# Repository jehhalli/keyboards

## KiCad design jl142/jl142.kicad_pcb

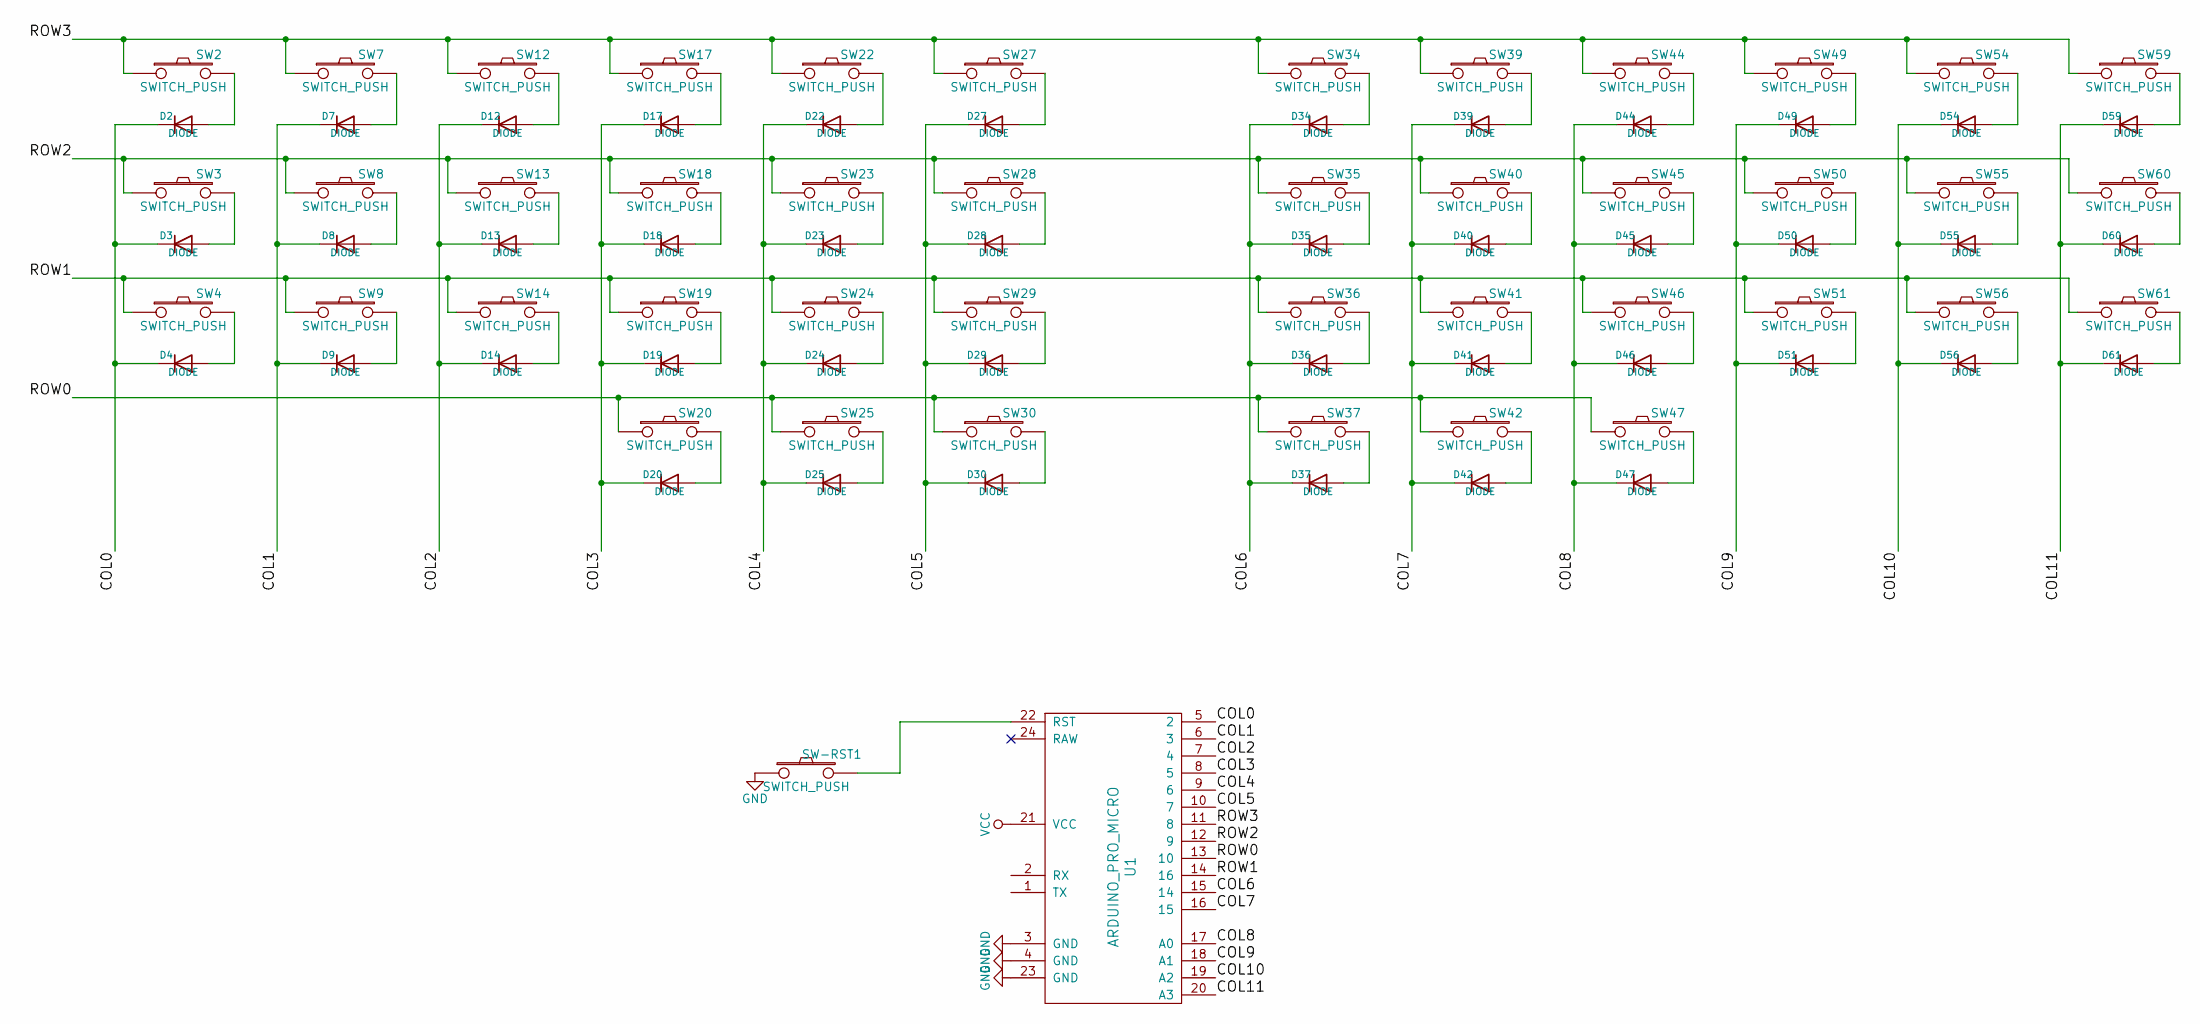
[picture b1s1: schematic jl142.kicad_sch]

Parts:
D2, D3, D4, D7, D8, D9, D12, D13, D14, D17, D18, D19, D20, D22, D23, D24, D25, D27, D28, D29, D30, D34, D35, D36, D37, D39, D40, D41, D42, D44, D45, D46, D47, D49, D50, D51, D54, D55, D56, D59, D60, D61: DIODE; D_DO-35_SOD27_P7.62mm_Horizontal
SW2, SW3, SW4, SW7, SW8, SW9, SW12, SW13, SW14, SW17, SW18, SW19, SW20, SW22, SW23, SW24, SW25, SW27, SW28, SW29, SW30, SW34, SW35, SW36, SW37, SW39, SW40, SW41, SW42, SW44, SW45, SW46, SW47, SW49, SW50, SW51, SW54, SW55, SW56, SW59, SW60, SW61: SWITCH_PUSH; Kailh_socket_PG1350_optional
SW-RST1: SWITCH_PUSH; reset_button
U1: ARDUINO_PRO_MICRO

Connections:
/COL0: D2.1 (K), D3.1 (K), D4.1 (K), U1.5 (2)
/COL1: D7.1 (K), D8.1 (K), D9.1 (K), U1.6 (3)
/COL2: D12.1 (K), D13.1 (K), D14.1 (K), U1.7 (4)
/COL3: D17.1 (K), D18.1 (K), D19.1 (K), D20.1 (K), U1.8 (5)
/COL4: D22.1 (K), D23.1 (K), D24.1 (K), D25.1 (K), U1.9 (6)
/COL5: D27.1 (K), D28.1 (K), D29.1 (K), D30.1 (K), U1.10 (7)
/COL6: D34.1 (K), D35.1 (K), D36.1 (K), D37.1 (K), U1.15 (14)
/COL7: D39.1 (K), D40.1 (K), D41.1 (K), D42.1 (K), U1.16 (15)
/COL8: D44.1 (K), D45.1 (K), D46.1 (K), D47.1 (K), U1.17 (A0)
/COL9: D49.1 (K), D50.1 (K), D51.1 (K), U1.18 (A1)
/COL10: D54.1 (K), D55.1 (K), D56.1 (K), U1.19 (A2)
/COL11: D59.1 (K), D60.1 (K), D61.1 (K), U1.20 (A3)
/ROW0: SW20.1, SW25.1, SW30.1, SW37.1, SW42.1, SW47.1, U1.13 (10)
/ROW1: SW4.1, SW9.1, SW14.1, SW19.1, SW24.1, SW29.1, SW36.1, SW41.1, SW46.1, SW51.1, SW56.1, SW61.1, U1.14 (16)
/ROW2: SW3.1, SW8.1, SW13.1, SW18.1, SW23.1, SW28.1, SW35.1, SW40.1, SW45.1, SW50.1, SW55.1, SW60.1, U1.12 (9)
/ROW3: SW2.1, SW7.1, SW12.1, SW17.1, SW22.1, SW27.1, SW34.1, SW39.1, SW44.1, SW49.1, SW54.1, SW59.1, U1.11 (8)
GND: SW-RST1.1, U1.3 (GND), U1.4 (GND), U1.23 (GND)
unnamed: D2.2 (A), SW2.2
unnamed: D3.2 (A), SW3.2
unnamed: D4.2 (A), SW4.2
unnamed: D7.2 (A), SW7.2
unnamed: D8.2 (A), SW8.2
unnamed: D9.2 (A), SW9.2
unnamed: D12.2 (A), SW12.2
unnamed: D13.2 (A), SW13.2
unnamed: D14.2 (A), SW14.2
unnamed: D17.2 (A), SW17.2
unnamed: D18.2 (A), SW18.2
unnamed: D19.2 (A), SW19.2
unnamed: D20.2 (A), SW20.2
unnamed: D22.2 (A), SW22.2
unnamed: D23.2 (A), SW23.2
unnamed: D24.2 (A), SW24.2
unnamed: D25.2 (A), SW25.2
unnamed: D27.2 (A), SW27.2
unnamed: D28.2 (A), SW28.2
unnamed: D29.2 (A), SW29.2
unnamed: D30.2 (A), SW30.2
unnamed: D34.2 (A), SW34.2
unnamed: D35.2 (A), SW35.2
unnamed: D36.2 (A), SW36.2
unnamed: D37.2 (A), SW37.2
unnamed: D39.2 (A), SW39.2
unnamed: D40.2 (A), SW40.2
unnamed: D41.2 (A), SW41.2
unnamed: D42.2 (A), SW42.2
unnamed: D44.2 (A), SW44.2
unnamed: D45.2 (A), SW45.2
unnamed: D46.2 (A), SW46.2
unnamed: D47.2 (A), SW47.2
unnamed: D49.2 (A), SW49.2
unnamed: D50.2 (A), SW50.2
unnamed: D51.2 (A), SW51.2
unnamed: D54.2 (A), SW54.2
unnamed: D55.2 (A), SW55.2
unnamed: D56.2 (A), SW56.2
unnamed: D59.2 (A), SW59.2
unnamed: D60.2 (A), SW60.2
unnamed: D61.2 (A), SW61.2
unnamed: SW-RST1.2, U1.22 (RST)
VCC: U1.21 (VCC)

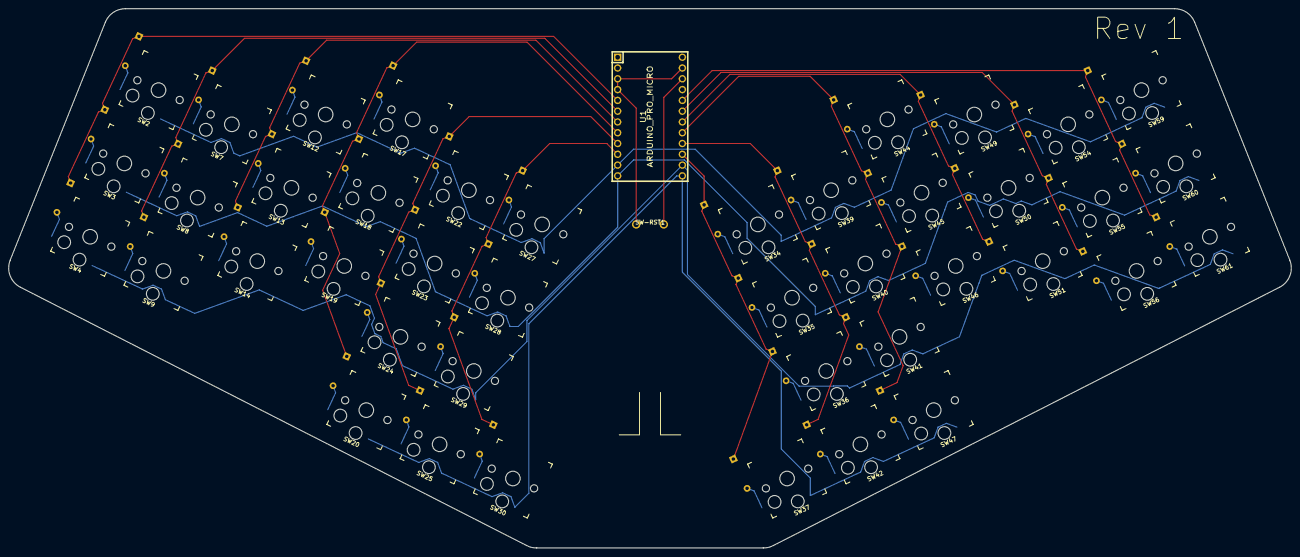
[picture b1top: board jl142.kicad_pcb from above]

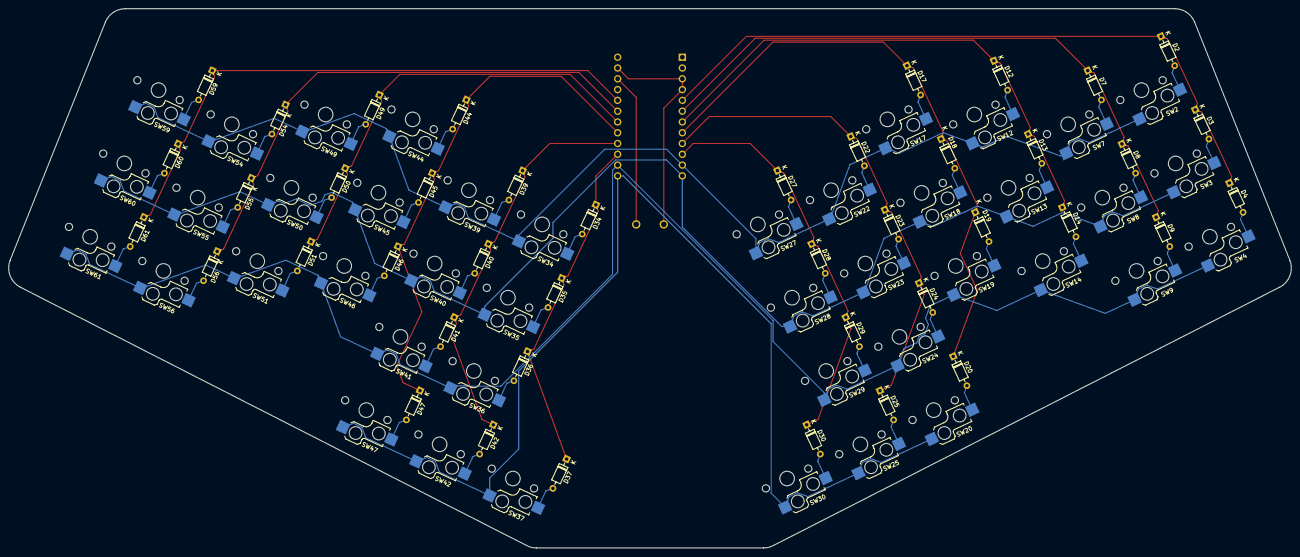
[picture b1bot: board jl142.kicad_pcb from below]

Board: 2 copper layers, 302.1 x 127.0 mm, 86 parts (42 on the bottom side), 60 nets.

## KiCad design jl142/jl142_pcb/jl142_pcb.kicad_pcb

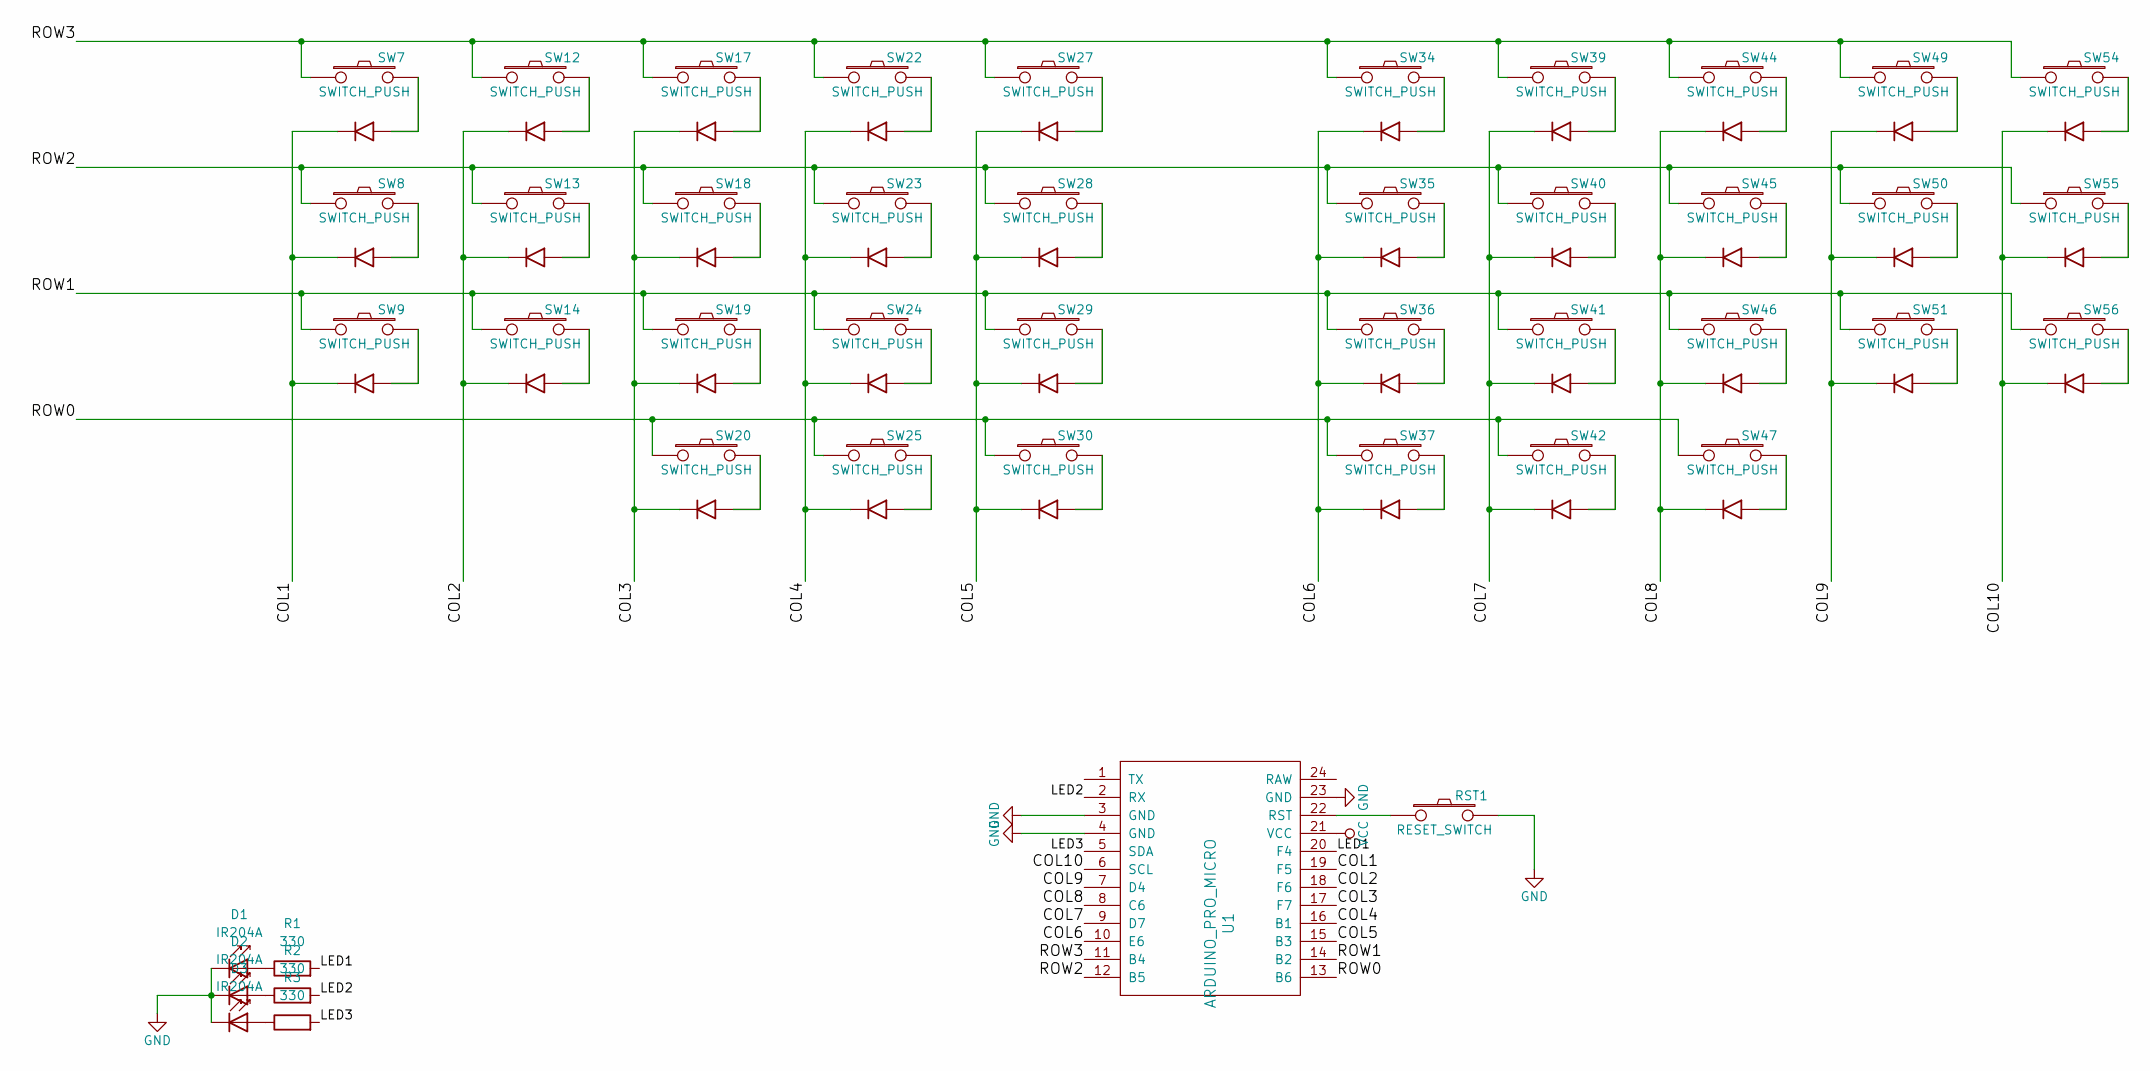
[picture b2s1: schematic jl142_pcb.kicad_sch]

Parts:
D1, D2, D3: IR204A; LED_D3.0mm_IRBlack
R1, R2, R3: 330; R_Axial_DIN0207_L6.3mm_D2.5mm_P7.62mm_Horizontal
RST1: RESET_SWITCH; reset_button
SW7, SW8, SW9, SW12, SW13, SW14, SW17, SW18, SW19, SW20, SW22, SW23, SW24, SW25, SW27, SW28, SW29, SW30, SW34, SW35, SW36, SW37, SW39, SW40, SW41, SW42, SW44, SW45, SW46, SW47, SW49, SW50, SW51, SW54, SW55, SW56: SWITCH_PUSH; cherry_hotswap_with_diode
U1: ARDUINO_PRO_MICRO

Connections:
/COL1: SW7.3 (K), SW8.3 (K), SW9.3 (K), U1.19 (F5)
/COL2: SW12.3 (K), SW13.3 (K), SW14.3 (K), U1.18 (F6)
/COL3: SW17.3 (K), SW18.3 (K), SW19.3 (K), SW20.3 (K), U1.17 (F7)
/COL4: SW22.3 (K), SW23.3 (K), SW24.3 (K), SW25.3 (K), U1.16 (B1)
/COL5: SW27.3 (K), SW28.3 (K), SW29.3 (K), SW30.3 (K), U1.15 (B3)
/COL6: SW34.3 (K), SW35.3 (K), SW36.3 (K), SW37.3 (K), U1.10 (E6)
/COL7: SW39.3 (K), SW40.3 (K), SW41.3 (K), SW42.3 (K), U1.9 (D7)
/COL8: SW44.3 (K), SW45.3 (K), SW46.3 (K), SW47.3 (K), U1.8 (C6)
/COL9: SW49.3 (K), SW50.3 (K), SW51.3 (K), U1.7 (D4)
/COL10: SW54.3 (K), SW55.3 (K), SW56.3 (K), U1.6 (SCL)
/LED1: R1.2, U1.20 (F4)
/LED2: R2.2, U1.2 (RX)
/LED3: R3.2, U1.5 (SDA)
/ROW0: SW20.1, SW25.1, SW30.1, SW37.1, SW42.1, SW47.1, U1.13 (B6)
/ROW1: SW9.1, SW14.1, SW19.1, SW24.1, SW29.1, SW36.1, SW41.1, SW46.1, SW51.1, SW56.1, U1.14 (B2)
/ROW2: SW8.1, SW13.1, SW18.1, SW23.1, SW28.1, SW35.1, SW40.1, SW45.1, SW50.1, SW55.1, U1.12 (B5)
/ROW3: SW7.1, SW12.1, SW17.1, SW22.1, SW27.1, SW34.1, SW39.1, SW44.1, SW49.1, SW54.1, U1.11 (B4)
GND: D1.1 (K), D2.1 (K), D3.1 (K), RST1.2, U1.3 (GND), U1.4 (GND), U1.23 (GND)
unnamed: D1.2 (A), R1.1
unnamed: D2.2 (A), R2.1
unnamed: D3.2 (A), R3.1
unnamed: RST1.1, U1.22 (RST)
VCC: U1.21 (VCC)

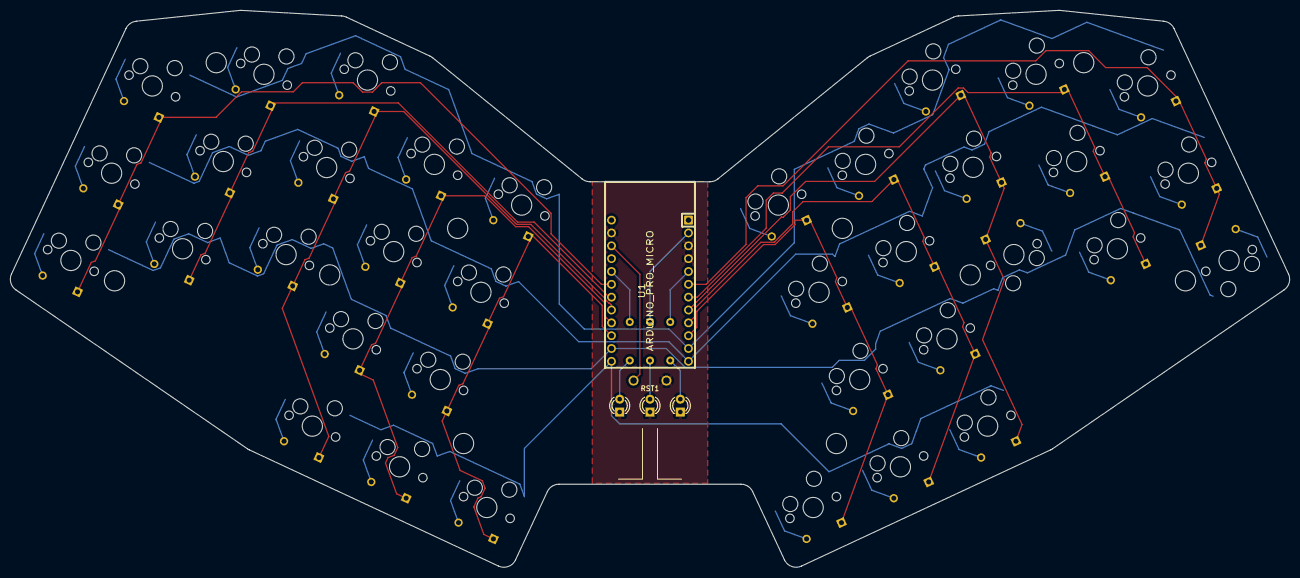
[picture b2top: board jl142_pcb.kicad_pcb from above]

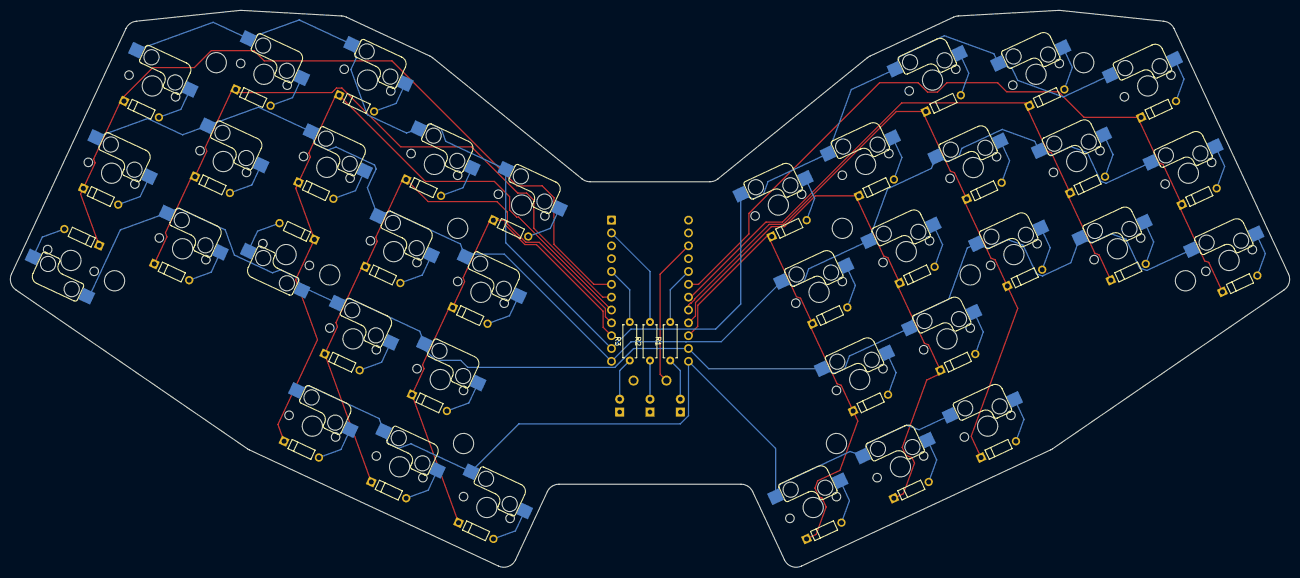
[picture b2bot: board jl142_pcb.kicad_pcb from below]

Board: 2 copper layers, 253.1 x 110.2 mm, 44 parts (3 on the bottom side), 22 nets.

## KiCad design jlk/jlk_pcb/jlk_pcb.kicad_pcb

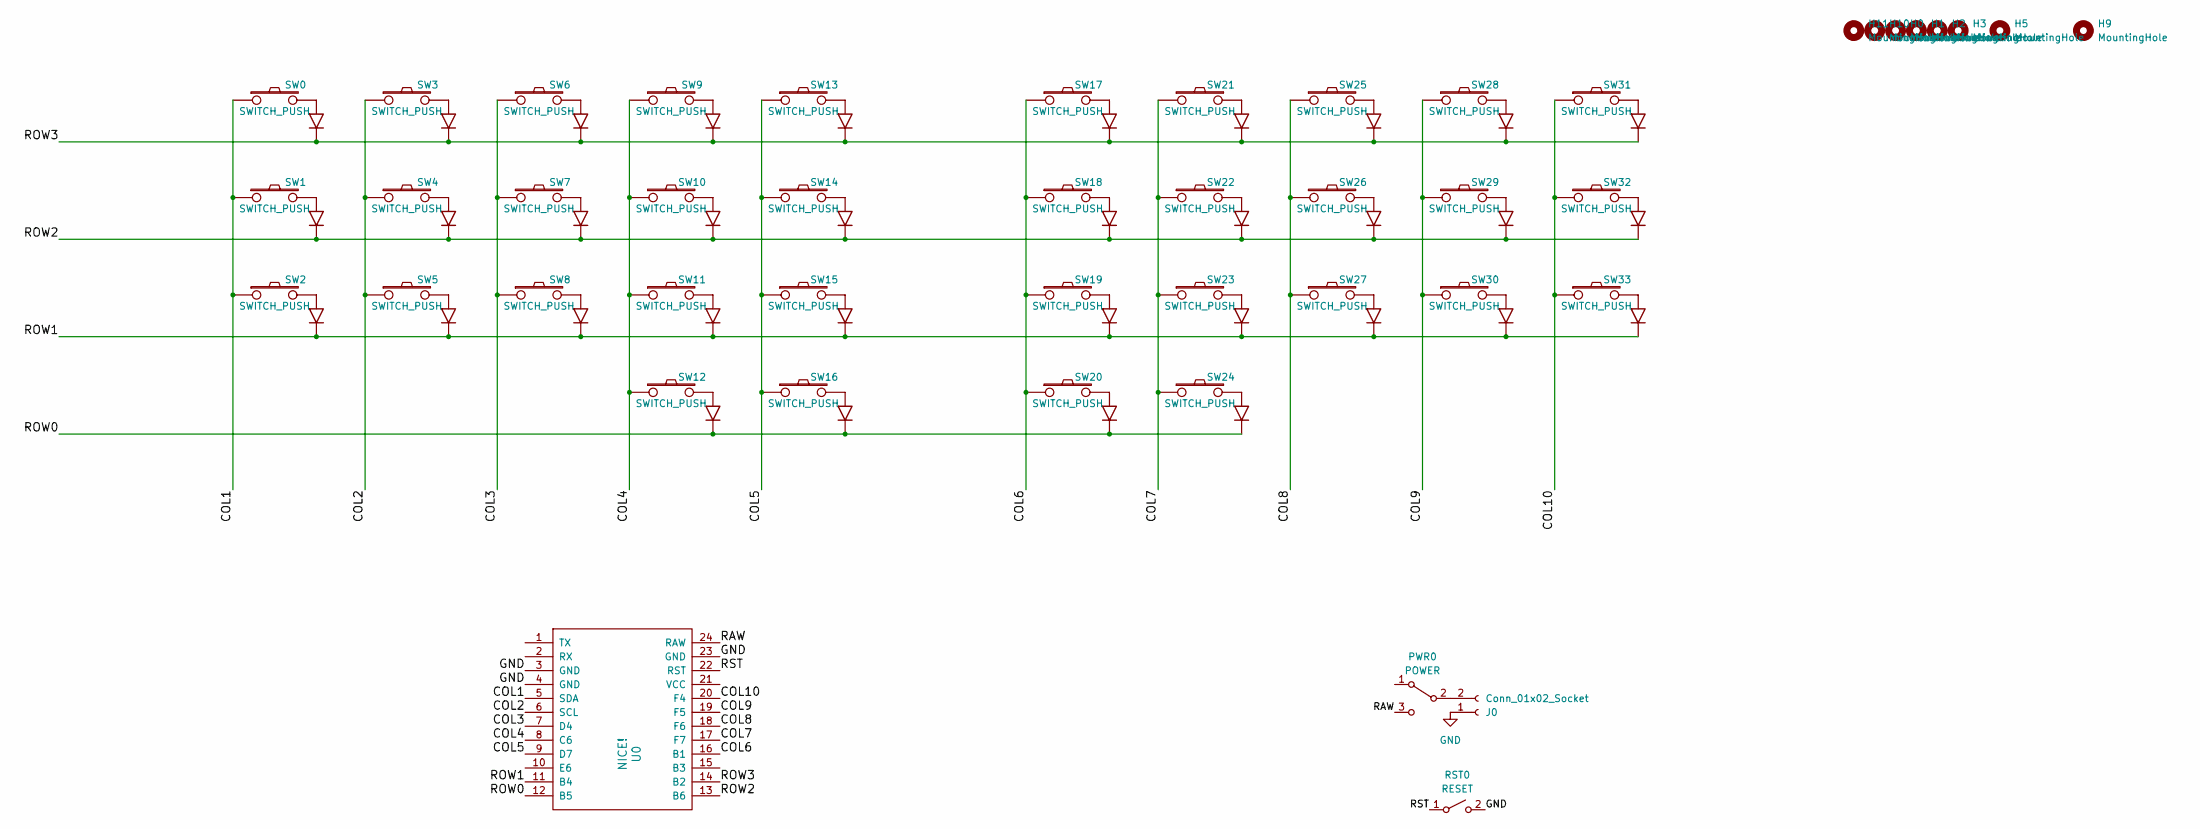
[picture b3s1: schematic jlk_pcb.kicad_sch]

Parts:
H0, H1, H2, H3, H5, H9, H10, H11: MountingHole; MountingHole_3.5mm
J0: Conn_01x02_Socket; jst_ph
PWR0: POWER; power_switch
RST0: RESET; reset_button_2
SW0, SW1, SW2, SW3, SW4, SW5, SW6, SW7, SW8, SW9, SW10, SW11, SW12, SW13, SW14, SW15, SW16, SW17, SW18, SW19, SW20, SW21, SW22, SW23, SW24, SW25, SW26, SW27, SW28, SW29, SW30, SW31, SW32, SW33: SWITCH_PUSH; cherry_hotswap_with_diode
U0: NICE!; nice!nano

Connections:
/COL1: SW0.1, SW1.1, SW2.1, U0.5 (SDA)
/COL2: SW3.1, SW4.1, SW5.1, U0.6 (SCL)
/COL3: SW6.1, SW7.1, SW8.1, U0.7 (D4)
/COL4: SW9.1, SW10.1, SW11.1, SW12.1, U0.8 (C6)
/COL5: SW13.1, SW14.1, SW15.1, SW16.1, U0.9 (D7)
/COL6: SW17.1, SW18.1, SW19.1, SW20.1, U0.16 (B1)
/COL7: SW21.1, SW22.1, SW23.1, SW24.1, U0.17 (F7)
/COL8: SW25.1, SW26.1, SW27.1, U0.18 (F6)
/COL9: SW28.1, SW29.1, SW30.1, U0.19 (F5)
/COL10: SW31.1, SW32.1, SW33.1, U0.20 (F4)
/RAW: PWR0.3 (C), U0.24 (RAW)
/ROW0: SW12.3 (K), SW16.3 (K), SW20.3 (K), SW24.3 (K), U0.12 (B5)
/ROW1: SW2.3 (K), SW5.3 (K), SW8.3 (K), SW11.3 (K), SW15.3 (K), SW19.3 (K), SW23.3 (K), SW27.3 (K), SW30.3 (K), SW33.3 (K), U0.11 (B4)
/ROW2: SW1.3 (K), SW4.3 (K), SW7.3 (K), SW10.3 (K), SW14.3 (K), SW18.3 (K), SW22.3 (K), SW26.3 (K), SW29.3 (K), SW32.3 (K), U0.13 (B6)
/ROW3: SW0.3 (K), SW3.3 (K), SW6.3 (K), SW9.3 (K), SW13.3 (K), SW17.3 (K), SW21.3 (K), SW25.3 (K), SW28.3 (K), SW31.3 (K), U0.14 (B2)
/RST: RST0.1 (A), U0.22 (RST)
GND: J0.1, PWR0.0, RST0.2 (B), U0.3 (GND), U0.4 (GND), U0.23 (GND)
unnamed: J0.2, PWR0.2 (B)

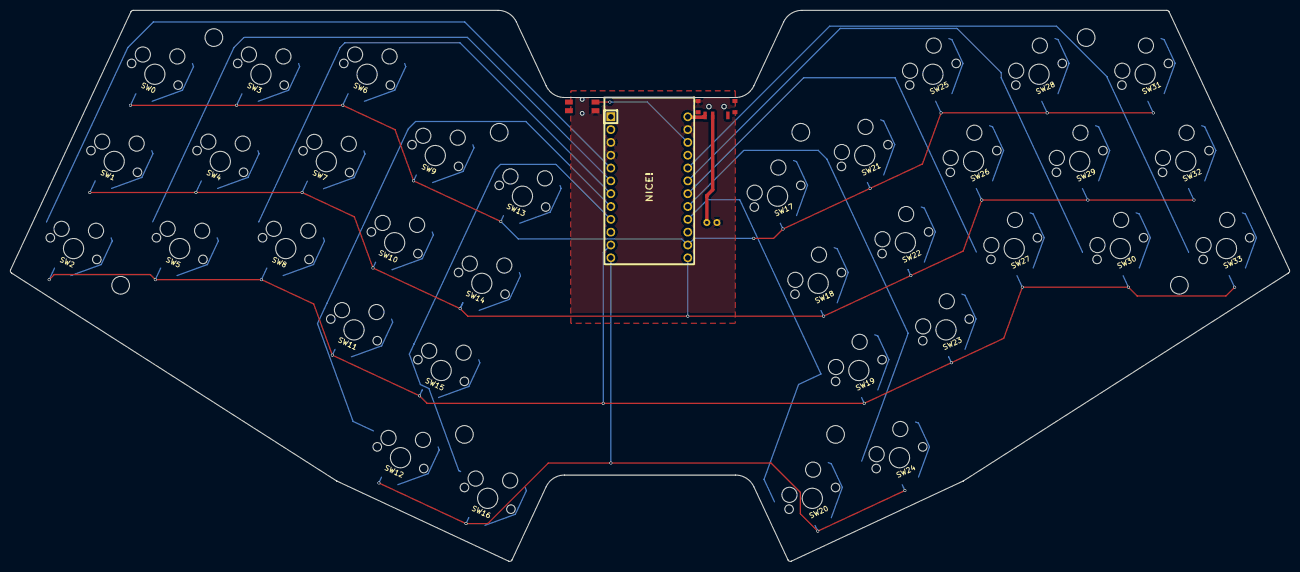
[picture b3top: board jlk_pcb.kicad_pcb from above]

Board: 2 copper layers, 253.4 x 109.2 mm, 46 parts (1 on the bottom side), 18 nets.
